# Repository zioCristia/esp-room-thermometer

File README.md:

# Esp room thermometer 

Esp8266-01 based module, 220V ac powered, for measuring room temperature for your autonomous house. 
Any possibility of improvement is accepted. 

## Table of contents 
* [General info](#general-info) 
* [Hardware](#hardware)
* [Software](#software) 
* [Pcb](#pcb) 
* [3D printed enclosure](#3d-printed-enclosure) 

## General info 

I built this module to have an inexpensive and reliable sensor in every room of my house.
Total cost per sensor is around 5.5€ and includes all components and pcb. It does not rely on batteries but on an ac-dc transformer type HLK-PM03.  

The design is intended to minimize the dimensions and thus be able to put the sensor inside the power boxes, where there are light switches to be clear. I 3D printed a container to be able to easily insert it in the boxes type btcino and allow the sensor to effectively detect the temperature and humidity outside through some openings. 

## Hardware 

The module is composed of: 
* esp8266-01 
* dht11 temperature and humidity sensor 
* hlk-pm03 as ac-dc transformer 
* 4.7k ohm resistor 
* 50uF capacitor 
  
I have also used a JST connector to bring 220v to the board. 

The esp is programmed before the insertion in the module thanks to a usb adapter, the following updates can be done over the air thanks to the EspHome software.  

I didn't want batteries to power the module so you don't have the bother of changing them and making sure they are charged, plus I think in the long run changing a battery every year or so is not convenient. 

However, if that is more suitable for you there will be no problems adding a battery holder and use a 3.3V battery. 

I know that DHT11 is not an exceptionally reliable temperature and humidity sensor but for the purpose of this project it is more than sufficient. 

For a complete list of parts with some links: https://docs.google.com/spreadsheets/d/1-pkWVYFf2BbrVPfpay5KMb0pS1-IxxCx1xM6d1OcC2A/edit#gid=0 

## Software 

The software used is EspHome to integrate the sensors with my HomeAssistant server but you may as well use another software to your liking. 

After adding your new esp device in EspHome, as a generic esp8266 board, the only thing to add in the code is the following: 

``` 

sensor: 

  - platform: dht 

    pin: GPIO2 

    temperature: 

      name: "Room temperature" 

    humidity: 

      name: "Room umidity" 

    update_interval: 60s 

``` 
This allows us to read the values of temperature and humidity and have them as a sensor in our Home Assistant server. 

You can add some [filters](https://esphome.io/components/sensor/index.html#sensor-filters) for calibrating dht, this should be done by comparison with a reliable thermometer. 

Check the [complete .yaml file](/room-temperature.yaml.example) if you need an example ready to use for your EspHome device. 

## Pcb 

The design of the pcb has been made with Eagle. The various components were added thanks to libraries found on the internet. 
For simplicity reasons all the components are through hole and the esp is inserted thanks to female socket header connectors. 

In one side of the pcb there are esp and dht11 and in the other hlk and a jst connector for power supply. The intention was to have all soldered on the board but the heat released by the hlk and the esp compromised the reading of temperature and umidity values. For this reason, dht sensor is installed thanks to 10cm cables soldered to the pcb. Some 3 way jst connector could be used to have a nicer design.  

The second version of the pcb allows to have larger distance between dht11 and other components and allows to have all soldered in the pcb. If you have more space available inside your switches box, it's preferable to use v2 (but it has not been tested yet). 

If you prefer to use battery power you can place a battery holder where there is the hlk and easily make a sensor like the ones ready to use with a lower overall cost. 

## 3D printed enclosure 

The purposes of the 3d enclosure are:  
- to maintain in a fix position the dht sensor 
- to allow proper measurements of the room temperature thanks to openings  
- to be able to place the module in a hidden way next to the power switches. 

In my home we have btcino switches, so a similar design was needed.

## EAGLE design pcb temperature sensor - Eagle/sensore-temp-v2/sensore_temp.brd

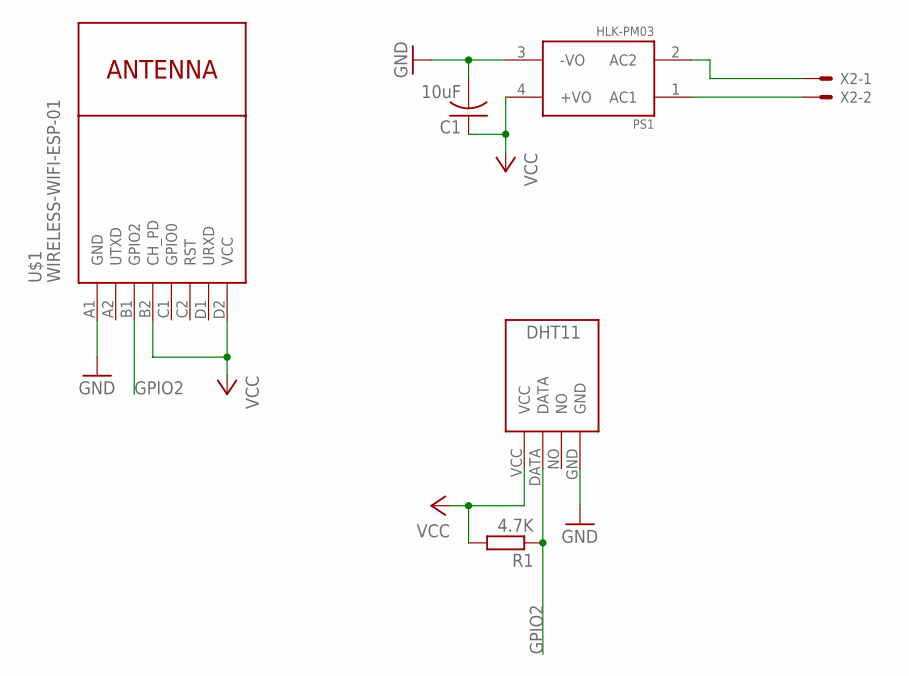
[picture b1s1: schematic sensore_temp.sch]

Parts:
C1: 10uF; C025-025X050
PS1: HLK-PM03; CONV_HLK-PM03
R1: 4.7K; 0204/7
U$1: WIRELESS-WIFI-ESP-01
U$2: DHT11
X2: JST-XH-02-PIN-LONG-PAD; JST-XH-02-PACKAGE-LONG-PAD

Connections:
GND: C1.2, PS1.3 (-VO), U$1.A1 (GND), U$2.GND
GPIO2: R1.1, U$1.B1 (GPIO2), U$2.DATA
unnamed: PS1.1 (AC1), X2.2
unnamed: PS1.2 (AC2), X2.1
VCC: C1.1, PS1.4 (+VO), R1.2, U$1.B2 (CH_PD), U$1.D2 (VCC), U$2.VCC

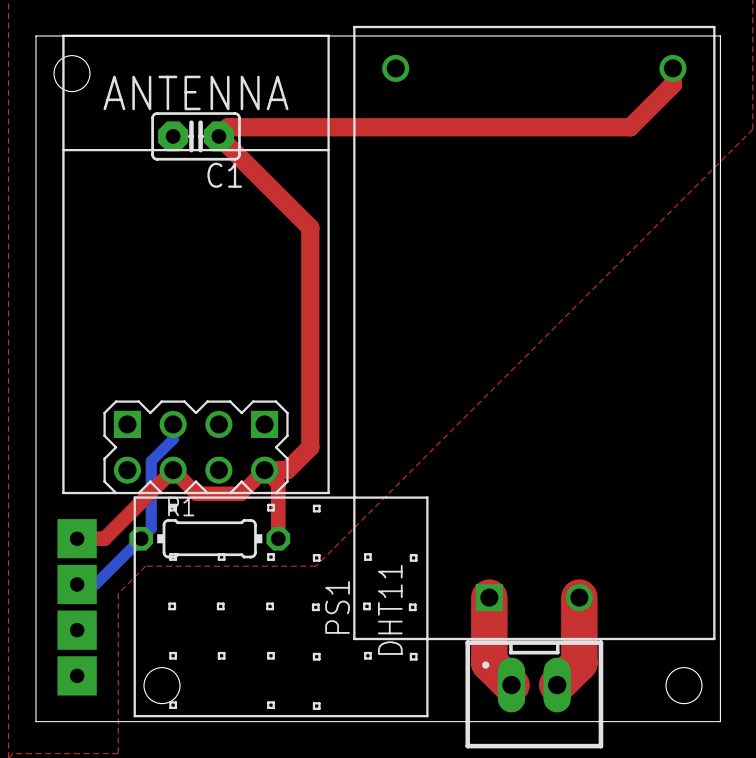
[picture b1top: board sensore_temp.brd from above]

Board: 2 copper layers, 38.0 x 38.1 mm, 6 parts (0 on the bottom side), 5 nets.

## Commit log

2025-05-25 Create LICENSE

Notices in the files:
parts and their libraries:
diy-modules: Released under the Creative Commons Attribution 4.0 International License: http://creativecommons.org/licenses/by/4.0
